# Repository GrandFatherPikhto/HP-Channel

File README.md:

# HP-Channel-v099 — UCC21750 driver for the CM200DU-24NFH IGBT module

*Читать по-русски: [README_ru.md](README_ru.md)*

The board drives one Mitsubishi CM200DU-24NFH half-bridge module from the HiPiMS-Controller-STM32-v099 controller
(Cyclone 10 LP). The controller does not change: the board plugs into its HP connector (IDC 2×7) exactly like the
power board with C2M0080120D SiC transistors. The goal is to keep the installation able to run on CM200DU-24NFH
modules, but with an isolated driver and desaturation protection instead of the non-isolated IR2110 / IR2213
drivers (§8, item 6).

The description follows the schematic as of netlist `HP-Channel-v099.net`, 16.11.2026 12:40. §3, §5 (items 1, 7)
and §6 were checked against the board and the netlist of 21.11.2026 17:40.

* §1–§3 — the module, the interfaces and the connections;
* §4 — design decisions already made;
* §5 — what is not in the schematic yet;
* §6 — layout and isolation: clearances, conformal coating, where 800 V can break through, running without the
  low-side arm;
* §7 — an open question about the controller;
* §8 — **questions about the installation that the component values depend on**.

The UCC21750 parameters were checked against the TI datasheet (2023 revision). Values marked **(check)** are given
from memory and must be checked against the relevant documents before ordering.

---

## 1. The CM200DU-24NFH module

```text
C1 ──┬── IGBT1 (G1/E1) ──┬── C2E1 ──┬── IGBT2 (G2/E2) ──┬── E2
     (DC+)                (output: midpoint)              (DC−)
```

* Power terminals (M6), per the drawing: **C2E1 — E2 — C1**.
* Control terminals — two pairs of 2.8 mm Faston tabs: **G1 + E1** (high-side IGBT), **G2 + E2** (low-side). E1
  and E2 are auxiliary (Kelvin) emitters; inside the module they are the same nodes as C2E1 and E2.

Datasheet parameters that shape the driver:

| Parameter | Value | What it means for the driver |
| --- | --- | --- |
| VCES | 1200 V | The DESAT circuit and the isolation clearances must take the full bus voltage |
| VGES | ±20 V | A +15 / −5 V gate supply is within limits |
| IC / ICM | 200 A / 400 A (pulse) | |
| VCE(sat) | 5.0 V typ., 6.5 V max. at 200 A, VGE = 15 V | Taken into account in the DESAT threshold (§4) |
| QG | 900 nC | Peak gate currents are a few amperes (§5) |
| External RG | 1.6 … 16 Ω | The chosen 10 Ω / 3.3 Ω are within the range |
| td(on) / tr | ≤ 300 ns / ≤ 80 ns | Fast entry into saturation — a short DESAT blanking time is acceptable |
| Note 4 | No short circuit capability is designed | Short-circuit withstand is not rated — the desaturation protection must trip as fast as possible |
| Switching test conditions | VGE = ±15 V | At −5 V the margin against false turn-on is smaller (§5, item 6) |

---

## 2. Interface to the controller (J1, IDC 2×7)

The board connects to the controller **through the HP-ISO-Channel adapter board** (`~/Projects/KiCad/HiPIMS/HP-ISO-Channel-v099`):

```text
controller J10/J11 (IDC 2×6, 3.3 V) ─► HP-ISO-Channel: ISO7740 / ISO7720 + B0505S ─► J2 (IDC 2×7) ─► J1 of this board
                            isolated domain +5V_IDC / GND_IDC
```

* HP-ISO-Channel galvanically separates the controller from the driver's primary side: arc currents and
  common-mode noise of the power stage do not reach the FPGA ground. The UCC21750 separates the primary side from
  the high-voltage arms.
* The `+5V_IDC` / `GND_IDC` domain is powered by the isolated B0505S DC/DC on HP-ISO-Channel; the CTL / RST signals
  come from SN74LVC1G17 buffers powered from +5V_IDC, and FLT is received by the same kind of buffer from +5V_IDC
  (with a 100 kΩ pull-down to GND_IDC on HP-ISO-Channel: a disconnected cable reads as a fault).
* So the logic on this connector is **5 V**, and the UCC21750 primary side is powered from +5V_IDC.

The J1 pinout matches J2 of HP-ISO-Channel. Signal lines alternate with ground.

| Pin | Net | Purpose |
| --- | --- | --- |
| 1, 3, 5, 7, 9, 11, 13 | `GND_IDC` | Isolated ground of the HP-ISO-Channel domain |
| 2 | `+5V_IDC` | UCC21750 primary-side supply (from the B0505S on HP-ISO-Channel) |
| 4 | `/CTL_A` | Channel A control (high-side IGBT) |
| 6 | `/RST_A` | Channel A fault reset / enable |
| 8 | `/FLT_A` | Channel A fault: open drain, active low |
| 10 | `/CTL_B` | Channel B control (low-side IGBT) |
| 12 | `/RST_B` | Channel B reset / enable |
| 14 | `/FLT_B` | Channel B fault |

**A direct connection to the controller's HP connector (J10 / J11) is not supported.** The connector fits
mechanically, but the controller's logic is 3.3 V (74HC14 powered from +3.3 V): the 5 V FLT pull-up on this board
exceeds the controller's input voltage limit, and the datasheet does not guarantee the UCC21750 input thresholds at
VCC = 5 V for a 3.3 V signal.

---

## 3. Connection to the module

Channel **A is the high-side IGBT (IGBT1)**, channel **B is the low-side one (IGBT2)**.

The installation's bus voltage is **800 V**.

Each arm has **one 4-position JST VH connector (B4P-VH)**: J2 for arm A, J3 for arm B. Position 2, between the
collector and the emitter, is empty: there is no pad 2 on the board, and pin 2 is removed from the header. Crimp
contacts were chosen over screw terminals because a screw clamp loosens over time and needs re-tightening.

| Connector | Pin | Board net | Module terminal |
| --- | --- | --- | --- |
| J2 (A) | 1 | `/SwitchA/DRAIN` (collector, DESAT) | C1 (M6 power terminal, DC+) |
| J2 (A) | 2 | — (no pad, pin removed) | — |
| J2 (A) | 3 | `/SwitchA/SOURCE` (emitter) | E1 (auxiliary) |
| J2 (A) | 4 | `/SwitchA/CLMPI` (gate) | G1 |
| J3 (B) | 1 | `/SwitchB/DRAIN` (collector, DESAT) | C2E1 (M6 power terminal, midpoint) |
| J3 (B) | 2 | — (no pad, pin removed) | — |
| J3 (B) | 3 | `/SwitchB/SOURCE` (emitter) | E2 (auxiliary) |
| J3 (B) | 4 | `/SwitchB/CLMPI` (gate) | G2 |

The DRAIN / SOURCE net names are kept from the SiC version; for an IGBT they are the collector / emitter.

* **C–E clearance at the connector.** Across C and E of an arm that is off sits the whole bus (800 V) plus the
  turn-off overshoot. This is functional insulation inside one circuit; the connector rating (250 V between
  adjacent contacts) does not apply to it — the distance decides. Contact centres 1 and 3 are 7.92 mm apart, the
  pins ≈ 6.8 mm apart in air, the pads 5.22 mm apart on the board. Per IPC-2221B that is ≈ 1040 V uncoated and more
  under conformal coating (§6.2) — with margin.
* **Pad 2 is missing on purpose.** A floating pad in the middle would cut the collector → emitter creepage path
  from 5.2 mm to 2 × 1.26 ≈ 2.5 mm.
* **Connect only with the bus discharged.** Contact 1 is at collector potential.
* **One connector per arm, not per module.** The high-side and low-side gates sit at different potentials (the
  midpoint and DC−). A shared header would join the A and B isolation zones on the board; so A and B are separate
  connectors, each in its own zone.
* **Position 2 of the mating housing carries no contact**, so the clearance is not defeated.
* **The collector wire must be high-voltage** (silicone or PTFE, 2–3 kV). Check that its cross-section and the
  outer insulation diameter fit the VH crimp contact (SVH) **(check)** against the contact's datasheet.
* **Gate / emitter** — a twisted pair, as short as possible. On the module side: G and E — insulated 2.8 mm
  Fastons; C — a ring terminal for the M6 power screw.
* **A / B marking.** The connectors are identical: on the silkscreen and on the cables — "A → C1 / E1 / G1",
  "B → C2E1 / E2 / G2". Swapped cables swap the arms' functions, and DESAT would measure the other arm.
* **The 24 V input (J5) is a DC barrel jack** instead of a 2-pin JST VH. The arm connectors are VH too, so a
  2-pin power plug could be pushed into a gate connector off by one position; a barrel jack makes that physically
  impossible. See §5, item 7.
* **CLMPI** (the active Miller clamp) is connected on the board to the gate node after R3 / R4 (R13 / R14). It is
  effective with short wires to the module (a few centimetres). With long wires the main protection against false
  turn-on is the negative gate bias.
* **The high-side arm floats:** the secondary side of channel A, including its DC/DC, sits at the midpoint
  potential and swings by the full bus voltage at every switching edge.
* **Without the low-side arm** the module's G2 gate must not be left floating — see §6.4.

---

## 4. Design decisions already made

* **Hardware half-bridge interlock.** The IN− input of channel A is connected to `/CTL_B`, the IN− of channel B
  to `/CTL_A`. The high-side and low-side IGBTs cannot be on at the same time, whatever the firmware does.
* **Fault signal.** The RDY and FLT outputs of each UCC21750 (open drain) are tied together: a secondary-side
  supply dropout is also reported to the controller as a fault.
* **Desaturation protection (DESAT):** two US1M diodes in series (2 kV), a 470 Ω resistor (1210), a 47 pF
  blanking capacitor, a BAT54S clamp between the emitter and +15 V.
  * UCC21750 parameters (TI datasheet, 2023 revision): charge current ICHG = 430 / 500 / 570 µA, threshold
    VDESAT = 8.5 / 9.15 / 9.8 V, internal leading-edge blanking tDESATLEB = 200 ns.
  * Blanking time ≈ 47 pF · 9.15 V / 500 µA ≈ 0.86 µs (0.7…1.07 µs over the spread) plus 200 ns. Given the
    module's fast turn-on (td(on) + tr < 0.4 µs) and the lack of a rated short-circuit withstand, it should not
    be made longer.
  * Threshold: the voltage at the DESAT input ≈ VCE + 2·Vf + 0.5 mA·470 Ω ≈ VCE + 1.8 V. With VDESAT = 9.15 V it
    trips at about VCE ≈ 7.3 V (6.7…8.0 V over the threshold spread), which on the output characteristic
    (VGE = 15 V) corresponds to ≈ 300 A. Whether that level is acceptable depends on the peak discharge currents (§8).
* **Gate resistors:** 10 Ω for turn-on (OUTH), 3.3 Ω for turn-off (OUTL).
* **Power:**
  * the secondary sides — isolated Murata MGJ2 +15 / −5 V DC/DCs (U1, U2) from a separate 24 V input (J5);
  * the 24 V domain is isolated both from the controller and from the arms;
  * the UCC21750 primary side is powered from the +5 V of the controller connector.
* AIN is tied to COM, APWM is unused. Decoupling capacitors sit at both sides of each UCC21750 and at each DC/DC.

---

## 5. What is not in the schematic yet

1. ~~Connectors to the module~~ — **done**: J2 / J3 B4P-VH, 1 — collector (`DRAIN`), 2 — none (pad and pin
   removed), 3 — emitter (`SOURCE`), 4 — gate (`CLMPI`), as in §3. (In the netlist of 16.11 14:18 they were J3 / J4
   with a different pinout; renamed and re-pinned by 21.11.)
2. **Done (netlist 16.11 14:45): R2 / R12.** **A 10 kΩ gate–emitter resistor on each arm** (between
   `/SwitchX/CLMPI` and `/SwitchX/SOURCE`) — holds the IGBT off with the connector unplugged or the driver
   unpowered. A resistor directly across the module's G–E terminals is also desirable.
3. **Logic levels are 5 V, matched to HP-ISO-Channel (§2); no LDO is needed.** The supply still has to be checked:
   * the B0505S is an unregulated converter: at light load its output rises. For the UCC21750 VCC the recommended
     range is 3.0…5.5 V, the absolute maximum 6 V; FLT and RDY must not exceed VCC. **Measure `+5V_IDC`** on an
     assembled HP-ISO-Channel with this board connected (the domain load is about 20–30 mA: two UCC21750, the
     buffers, ISO77xx, an LED, the 1 kΩ load resistor R3). Above 5.5 V — add pre-load or put a 5 V regulator after
     the B0505S.
4. **Input pull-ups/downs.** The UCC21750 has internal ones: IN+ to GND ≈ 55 kΩ, IN− to VCC ≈ 55 kΩ, RST/EN to
   GND ≈ 50 kΩ; with a broken cable the output is held low and the driver is off. External 10 kΩ to `GND_IDC` on
   IN+ and RST/EN are not required; with a long cable to the controller they help as a stiffer pull-down against
   pick-up.
5. **Done (14:45): R3 / R4, R13 / R14 in 1206.** **Gate resistors in a 1206 package, preferably pulse-rated.**
   Peak turn-off current ≈ (15 + 5) V / 3.3 Ω ≈ 6 A at QG = 900 nC.
6. **Negative gate bias.** The module's switching characteristics are rated at ±15 V. If an MGJ2-series converter
   with +15 / −8 (−9) V in the same package is available, it is preferable to −5 V.
7. **The 24 V input is a DC barrel jack** instead of a 2-pin JST VH. Done (14:45): J5 GCT DCJ200-10-A
   (5.5 / 2.1 mm).
   * a jack rated at least 24 V, with current margin for two MGJ2 **(check)**;
   * the centre contact is "+": the ⊖-◎-⊕ polarity symbol on the silkscreen next to J5;
   * no reverse-polarity protection is fitted: the board is powered from the installation's own supply. If any
     adapter may be used (some have "−" in the centre), a series Schottky diode is needed before C1 — the MGJ2
     inputs are not protected against reverse polarity.

---

## 6. Layout and isolation

The board has two layers. The isolation clearances are set by the rules file `HP-Channel-v099.kicad_dru` (the
domains are defined by net names, no net classes needed). On refill (B) the pours pull back by these rules on
their own; DRC checks them.

### 6.1 Domains and clearances

* **Primary side:** `GND_IDC`, `+5V_IDC`, `/CTL_x`, `/RST_x`, `/FLT_x` and the UCC21750 inputs that live on the
  arm sheets (`/SwitchX/CTL_P`, `/SwitchX/CTL_N`, `/SwitchX/RST_SN`); separately — the 24 V domain (`+24V`,
  `GND_24V`).
* **Arm A:** `/SwitchA/*` and the nets of its LEDs and diodes; **arm B:** `/SwitchB/*` and the same.
* **The collector net** — everything at collector potential: `/SwitchX/DRAIN` and the DESAT chain beyond the
  first diode's cathode — `Net-(D4-K)`, `Net-(D5-K)` (arm A), `Net-(D10-A)`, `Net-(D10-K)` (arm B). On the board this
  is one small spot per arm: contact 1 of the connector, R11 / R21, D4–D5 / D9–D10.

| Between | Clearance | Rule in `.kicad_dru` |
| --- | --- | --- |
| arm A ↔ arm B | 2 mm | `arm A to arm B` |
| arm ↔ primary side | 2.5 mm | `arm A to primary`, `arm B to primary` |
| collector net ↔ the rest of its arm | 2.5 mm | `HV to its arm` |
| IDC ↔ 24 V | 0.5 mm (functional insulation) | `IDC to 24V` |
| a DESAT diode's own pads (SMA) | 1.4 mm | `DESAT diode own pads` |

Between the gate (`CLMPI`) and the emitter (`SOURCE`) of one arm there are at most 20 V (+15 / −5 V): the ordinary
clearance applies there.

### 6.2 Why the clearances are what they are, and why coating is required

* IPC-2221B, table 6-1, external conductors above 500 V: **uncoated (B2) — 0.005 mm/V**, **under a permanent
  polymer coating (B4) — 0.00305 mm/V**.
* 2.5 mm under coating is ≈ 820 V: at an 800 V bus the margin is only 2–3 %. The same 2.5 mm uncoated is 500 V.
* 2 mm under coating is ≈ 650 V: the clearance between the arms is about 20 % below IPC, accepted deliberately
  (see below). It only matters when J3 is connected (§6.3, item 3).
* So **the whole board is conformally coated**; without coating these clearances are not acceptable. The figures
  refer to the working voltage; the table does not cover short turn-off overshoots.
* The basis for the small clearances is experience: a driver on the IR2213 (2.54 mm between pins) ran in the
  installation for about 10 years without breakdowns.
* The closely spaced UCC21750 pins are no argument here: adjacent pins on one side (1.27 mm pitch) are nets of one
  arm with at most 20 V between them; across the barrier the DW-16 package gives 7.5 mm between pins; the DESAT pin
  is low-voltage — 800 V only appears beyond the cathode of D4 (D9), outside the chip.

### 6.3 Where 800 V can break through

While the high-side switch is off:

1. **Inside arm A: collector net → the rest of the arm.** The main direction. DRAIN, the cathodes of D4 / D5 and
   R11 sit at +800 V relative to SOURCE, and 2.5 mm away is everything referenced to the emitter:
   * **into the gate (`CLMPI`)** — the IGBT gate oxide breaks down, the switch turns on or fails short, the UCC21750
     outputs burn;
   * **into `SOURCE`** — the bus current bypasses the IGBT through a board trace; the desaturation protection does
     not see it (no current flows through the switch); the trace vaporises, a fire is possible;
   * **into +15 / −5 V** — the MGJ2 output and the UCC21750 supply burn.

   The same applies to arm B when it is fitted and the low-side switch is off.
2. **Arm A → primary side.** The whole secondary side of A floats with the midpoint between DC− and DC+. If the
   controller or DC− is earthed, up to 800 V can appear between arm A and `GND_IDC`. The weak spot is where the
   pours come within 2.5 mm; the UCC21750 and the MGJ2 have their own barriers. HP-ISO-Channel stands further along,
   so this will probably not reach the FPGA, but it will destroy the primary side of this board.
3. **Arm A → arm B (2 mm).** Depends on J3. If it is connected to G2 / E2, arm B's copper sits at DC− and arm A at
   the midpoint: up to 800 V across 2 mm, below IPC even under coating. If J3 is not connected, arm B's copper
   floats and there is no hazard.

### 6.4 Running without the low-side arm

The CM200DU-24NFH is a half bridge: the low-side IGBT stays in the package even if arm B is not used. **The G2 gate
must not be left floating:** the dv/dt edge of every high-side switching event charges it through the Miller
capacitance, the low-side switch partly turns on, and shoot-through current flows through the half bridge.
Options:

* **short G2 to E2 right at the module** — with a jumper across the Fastons or a resistor of 10 kΩ or less. Then do
  not connect J3: no cable runs to arm B, and item 3 of §6.3 disappears. R12 on the board does not help here — it
  sits on the board, not on the module;
* **or fit arm B completely and hold `/CTL_B` low:** the driver keeps −5 V on the gate and the Miller clamp works.
  More robust, but needs the second MGJ2 and all of its parts.

### 6.5 Other notes

* **There are no slots** under the UCC21750 or at the connectors: isolation relies on distance and coating.
* **Mounting holes:** H1 / H2 are on `GND_IDC`, H3 / H4 have no net.
* **The gate loop** (OUTH / OUTL → R3 / R4 → gate → module → emitter → COM / VEE) — minimum area, 0.65 mm
  traces.
* **Open items:**
  * the coating area on a user layer, labelled "Conformal coating";
  * the 100 nF VDD / VEE decoupling (C9 / C10, C25 / C26) is on the bottom, 4.2 mm from pins 5 and 8, through
    vias; better on top, within 1–2 mm;
  * C19 / C35 (DESAT blanking, 47 pF) are 6–8 mm from the DESAT pin; move them next to the DESAT / COM pins,
    otherwise pick-up on the long branch may cause false protection trips.

---

## 7. Controller: output state at power-up

According to the available information **(check)** in the Cyclone 10 LP Handbook, the FPGA user pins have weak
pull-ups during configuration. There are currently no resistors between the FPGA and the 74HC14 buffers on the
`HP.x.CTL` / `HP.x.RST` lines. In that case the CTL signals of both channels are active while the FPGA loads.
The interlock on the driver board (§4) rules out shoot-through in the half bridge, but one of the switches can still
turn on at power-up — for this board and for the SiC version alike.

The proposed fix is ~2.2 kΩ resistors to ground on all `HP.x.CTL` and `HP.x.RST` lines on the FPGA side
(8 resistors).

---

## 8. Questions about the installation

The DESAT values, the DC/DC choice and the mechanical design depend on the answers:

1. **Peak discharge pulse current** (and the arc current before the protection trips): does it stay within the
   ≈ 300 A the DESAT threshold is set for (§4)?
2. **Bus voltage** — 800 V (taken into account in §3 and §6). Find out the size of the turn-off and arc overshoots,
   if they were measured: at 800 V the clearances of §6 work with almost no margin.
3. **Pulse length and repetition rate** — to estimate the driver power and the module heating.
4. **Which switches of the module are used** in the installation: both (half bridge) or one; what the second one
   does. If the low-side arm is not fitted — how the G2 gate is shorted (§6.4).
5. **Distance from the driver board to the module:** can the board be mounted directly on the module terminals
   (this decides how useful the Miller clamp is and what negative bias is needed)?
6. **Experience with the previous versions:** first an IR2110 was fitted — it failed systematically; then the
   IR2213, which ran for about 10 years. In which modes did the IR2110 fail (arcs, power-up, long operation), and
   what changed with the IR2213? The design assumes the main cause was the lack of isolation and desaturation
   protection; confirmation or a different picture will affect the decisions of §4–§5.

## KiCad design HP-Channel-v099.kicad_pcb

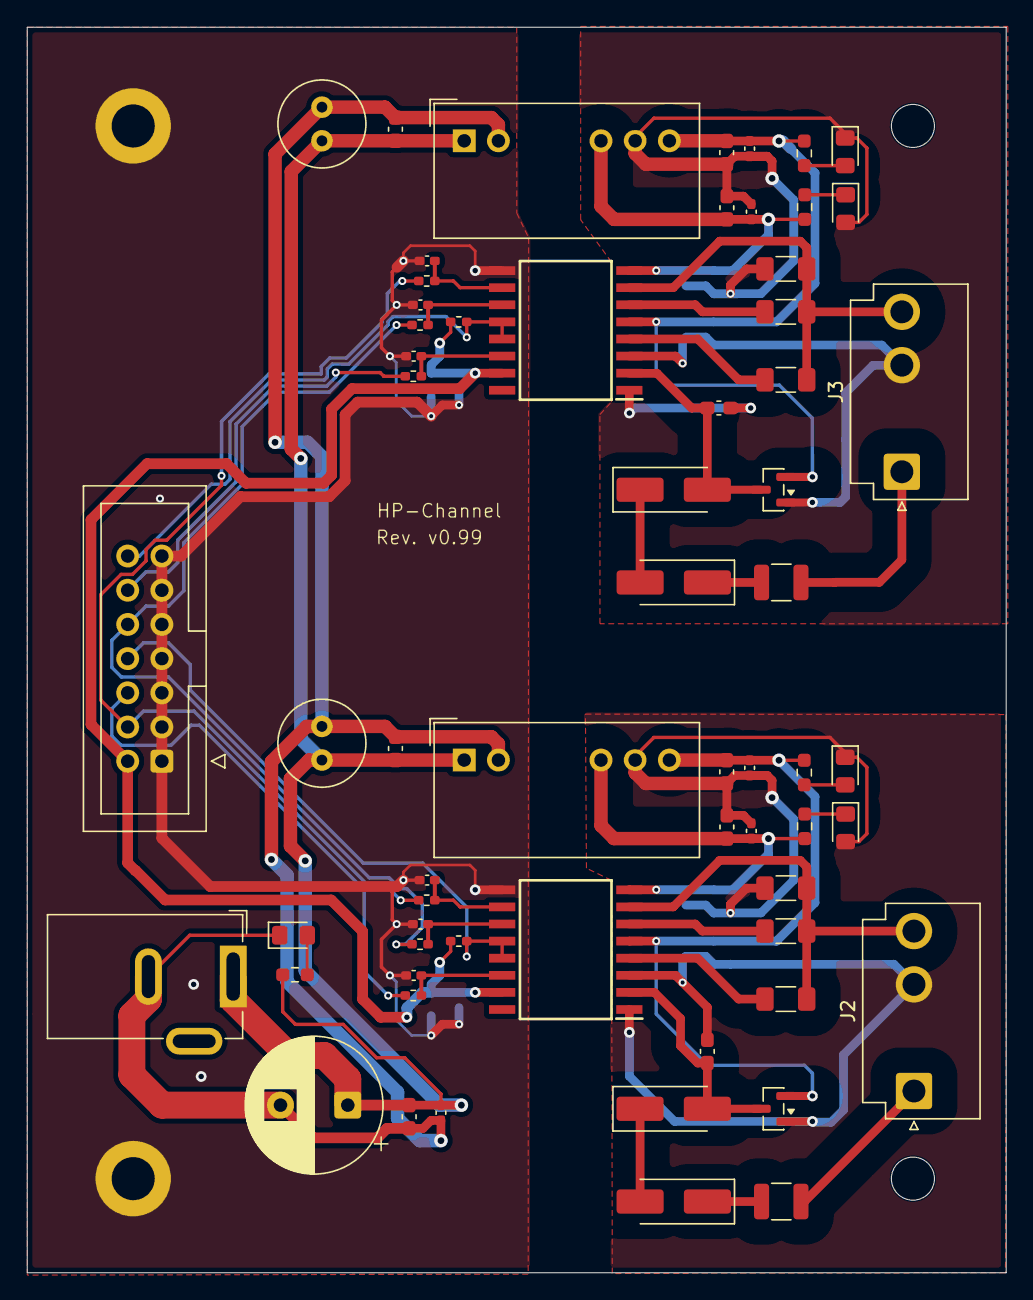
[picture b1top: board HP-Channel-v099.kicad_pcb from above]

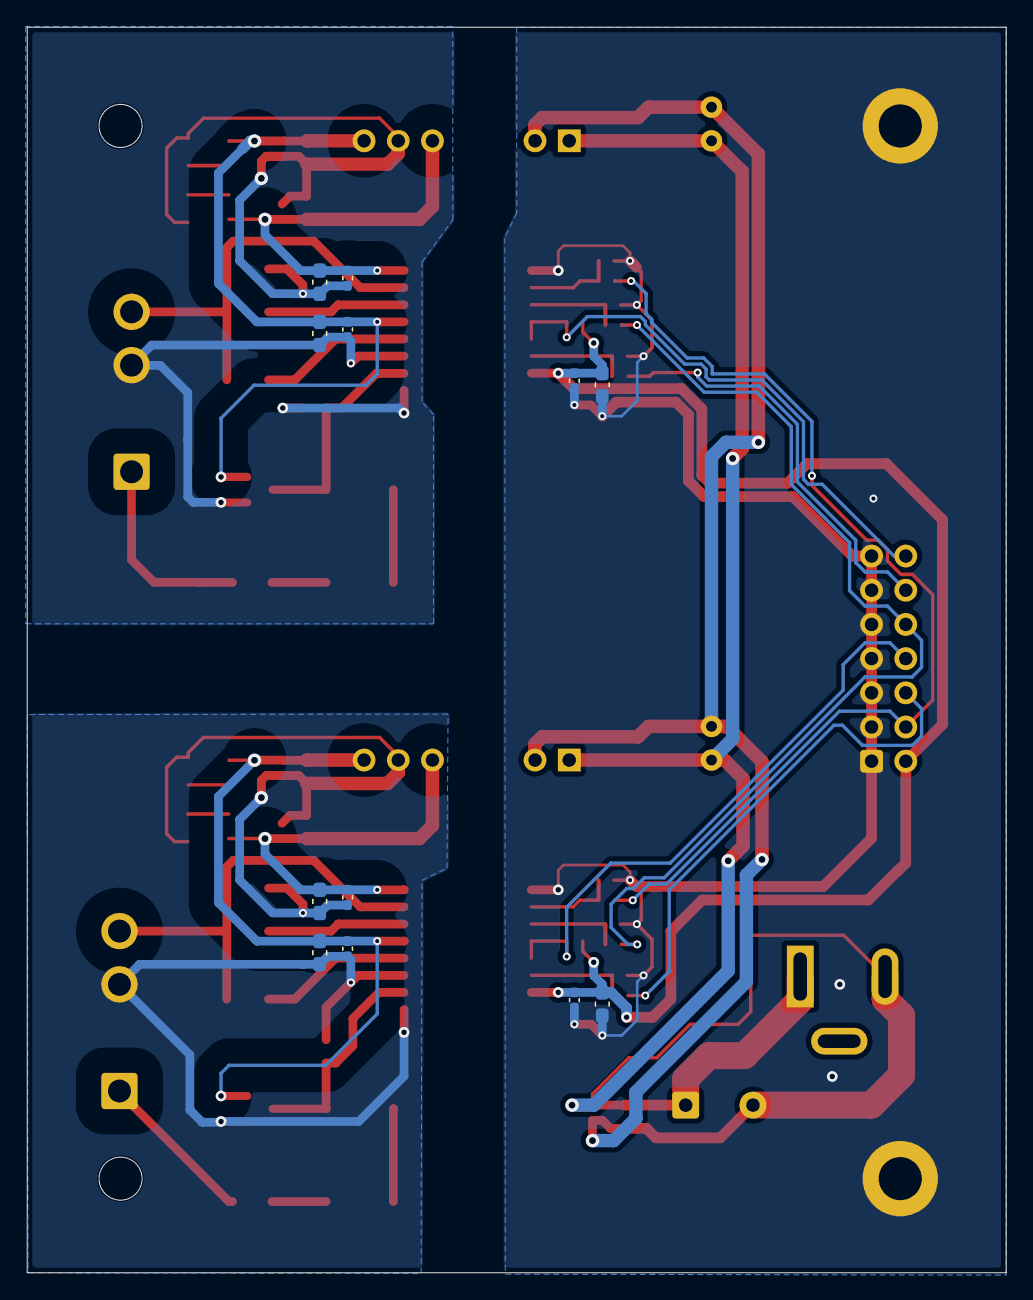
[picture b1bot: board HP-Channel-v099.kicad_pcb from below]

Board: 2 copper layers, 72.7 x 92.5 mm, 79 parts (12 on the bottom side), 41 nets.

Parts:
C1: 470 uF 50V; CP_Radial_D10.0mm_P5.00mm
C2, C5, C6, C18, C21, C22, C34: 10 uF; C_0603_1608Metric_Pad1.08x0.95mm_HandSolder
C3, C9, C10, C15, C16, C17, C25, C26, C31, C32, C33: 100 nF; C_0402_1005Metric_Pad0.74x0.62mm_HandSolder
C4, C20: 47 uF 50V; C_Radial_D6.3mm_H11.0mm_P2.50mm
C7, C11, C12, C23, C27, C28: 1 nF; C_0402_1005Metric_Pad0.74x0.62mm_HandSolder
C8, C24: 10 uF 50V; C_0603_1608Metric_Pad1.08x0.95mm_HandSolder
C13, C14, C29, C30: 10 uF 16V; C_0603_1608Metric_Pad1.08x0.95mm_HandSolder
C19, C35: 47 pF; C_0603_1608Metric_Pad1.08x0.95mm_HandSolder
D1, D2, D3, D7, D8: LED; LED_0805_2012Metric_Pad1.15x1.40mm_HandSolder
D4, D5, D9, D10: US1M; D_SMA_Handsoldering
D6, D11: BAT54S; SOT-23
H1, H2: MountingHole_Pad; MountingHole_3.2mm_M3_DIN965_Pad
H3, H4: MountingHole; MountingHole_3.2mm_M3_ISO14580
IC1, IC2: UCC21750QDWRQ1; SOIC127P1030X265-16N
J1: Conn HP Out; IDC-Header_2x07_P2.54mm_Vertical
J2, J3: Signal Out; JST_VH_B4P-VH_1x04_P3.96mm_Vertical
J5: P24V In; BarrelJack_GCT_DCJ200-10-A_Horizontal
R1, R8, R18: 10K; R_0603_1608Metric_Pad0.98x0.95mm_HandSolder
R2, R12: 10K; R_1206_3216Metric_Pad1.30x1.75mm_HandSolder
R3, R13: 10; R_1206_3216Metric_Pad1.30x1.75mm_HandSolder
R4, R14: 3.3; R_1206_3216Metric_Pad1.30x1.75mm_HandSolder
R5, R6, R7, R15, R16, R17: 100R; R_0402_1005Metric_Pad0.72x0.64mm_HandSolder
R9, R19: 5K1; R_0402_1005Metric_Pad0.72x0.64mm_HandSolder
R10, R20: 1K5; R_0603_1608Metric_Pad0.98x0.95mm_HandSolder
R11, R21: 470R; R_1210_3225Metric
U1, U2: DCDC 24 +15/-5; Converter_DCDC_Murata_MGJ2DxxxxxxSC_THT

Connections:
+5V_IDC: C17.1, C18.1, C33.1, C34.1, IC1.15 (VCC), IC2.15 (VCC), J1.2, R9.2, R19.2
+24V: C1.1, C2.1, C3.1, C4.1, C8.1, C20.1, C24.1, J5.1, R1.1, U1.1 (+VIN), U2.1 (+VIN)
/CTL_A: J1.4, R5.1, R15.1
/CTL_B: J1.10, R6.1, R16.1
/FLT_A: IC1.12 (RDY), IC1.13 (~FLT), J1.8, R9.1
/FLT_B: IC2.12 (RDY), IC2.13 (~FLT), J1.14, R19.1
/RST_A: J1.6, R7.1
/RST_B: J1.12, R17.1
/SwitchA/+15V: C5.1, C9.1, C13.1, C15.1, D6.2 (K), IC1.5 (VDD), R8.1, U1.7 (+VOUT)
/SwitchA/-5V: C6.1, C10.1, C14.1, C16.1, IC1.8 (VEE), R10.1, U1.5 (-VOUT)
/SwitchA/CLMPI: IC1.7 (CLMPI), J2.4, R2.1, R3.2, R4.1
/SwitchA/CTL_N: C11.1, IC1.11 (IN-), R6.2
/SwitchA/CTL_P: C7.1, IC1.10 (IN+), R5.2
/SwitchA/DESAT: C19.1, D4.2 (A), D6.3 (COM), IC1.2 (DESAT)
/SwitchA/DRAIN: J2.1, R11.2
/SwitchA/OUTH: IC1.4 (OUTH), R3.1
/SwitchA/OUTL: IC1.6 (OUTL), R4.2
/SwitchA/RST_SN: C12.1, IC1.14 (~RST/EN), R7.2
/SwitchA/SOURCE: C5.2, C6.2, C9.2, C10.2, C13.2, C14.2, C15.2, C16.2, C19.2, D2.1 (K), D3.2 (A), D6.1 (A), IC1.1 (AIN), IC1.3 (COM), J2.3, R2.2, U1.6 (0V)
/SwitchB/+15V: C21.1, C25.1, C29.1, C31.1, D11.2 (K), IC2.5 (VDD), R18.1, U2.7 (+VOUT)
/SwitchB/-5V: C22.1, C26.1, C30.1, C32.1, IC2.8 (VEE), R20.1, U2.5 (-VOUT)
/SwitchB/CLMPI: IC2.7 (CLMPI), J3.4, R12.1, R13.2, R14.1
/SwitchB/CTL_N: C27.1, IC2.11 (IN-), R16.2
/SwitchB/CTL_P: C23.1, IC2.10 (IN+), R15.2
/SwitchB/DESAT: C35.1, D9.2 (A), D11.3 (COM), IC2.2 (DESAT)
/SwitchB/DRAIN: J3.1, R21.2
/SwitchB/OUTH: IC2.4 (OUTH), R13.1
/SwitchB/OUTL: IC2.6 (OUTL), R14.2
/SwitchB/RST_SN: C28.1, IC2.14 (~RST/EN), R17.2
/SwitchB/SOURCE: C21.2, C22.2, C25.2, C26.2, C29.2, C30.2, C31.2, C32.2, C35.2, D7.1 (K), D8.2 (A), D11.1 (A), IC2.1 (AIN), IC2.3 (COM), J3.3, R12.2, U2.6 (0V)
GND_24V: C1.2, C2.2, C3.2, C4.2, C8.2, C20.2, C24.2, D1.1 (K), J5.2, U1.2 (-VIN), U2.2 (-VIN)
GND_IDC: C7.2, C11.2, C12.2, C17.2, C18.2, C23.2, C27.2, C28.2, C33.2, C34.2, H1.1 (1_1), H2.1 (1_1), IC1.9 (GND), IC2.9 (GND), J1.1, J1.3, J1.5, J1.7, J1.9, J1.11, J1.13
unnamed: D1.2 (A), R1.2
unnamed: D2.2 (A), R8.2
unnamed: D3.1 (K), R10.2
unnamed: D4.1 (K), D5.2 (A)
unnamed: D5.1 (K), R11.1
unnamed: D7.2 (A), R18.2
unnamed: D8.1 (K), R20.2
unnamed: D9.1 (K), D10.2 (A)
unnamed: D10.1 (K), R21.1
